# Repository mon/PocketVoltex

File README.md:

# Pocket Voltex

A tiny controller for K-Shoot MANIA/Sound Voltex or other similar games

## Project status
There is a major revision coming sometime 2021 but I estimate requires 50+ hours
to complete design. It will significantly improve manufacturing efficiency and hopefully
allow me to sell controllers while working full-time.

Please don't hold your breath on a timely release, but I have not forgotten this
project.

## Documentation
[DIY Kit assembly](Docs/Assembly.md)  
[(Old version)DIY Kit assembly](Docs/Assembly_old.md)

[Controller configuration](Docs/Configuration.md)

## Features
* Gateron mechanical switches
* Rock solid Bourns encoders with hardware smoothing
* 8 RGB LEDs
* Beautiful laser cut acrylic case
* Custom aluminium knobs by DJ Dao
* Acts as a gamepad or keyboard/mouse (KSM)
* HID Lighting support
* Configurable card/pin macro key
* Chrome configurator
* No drivers required!

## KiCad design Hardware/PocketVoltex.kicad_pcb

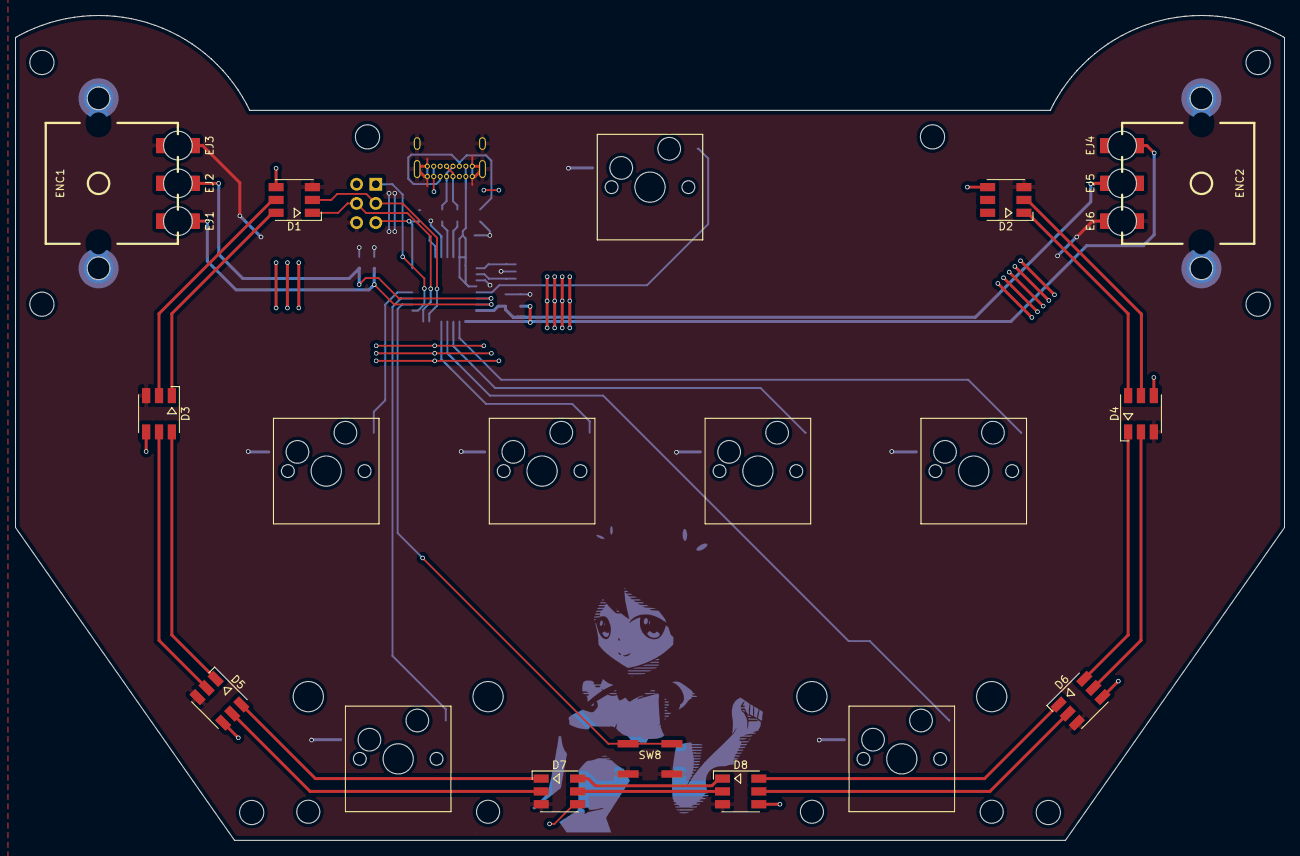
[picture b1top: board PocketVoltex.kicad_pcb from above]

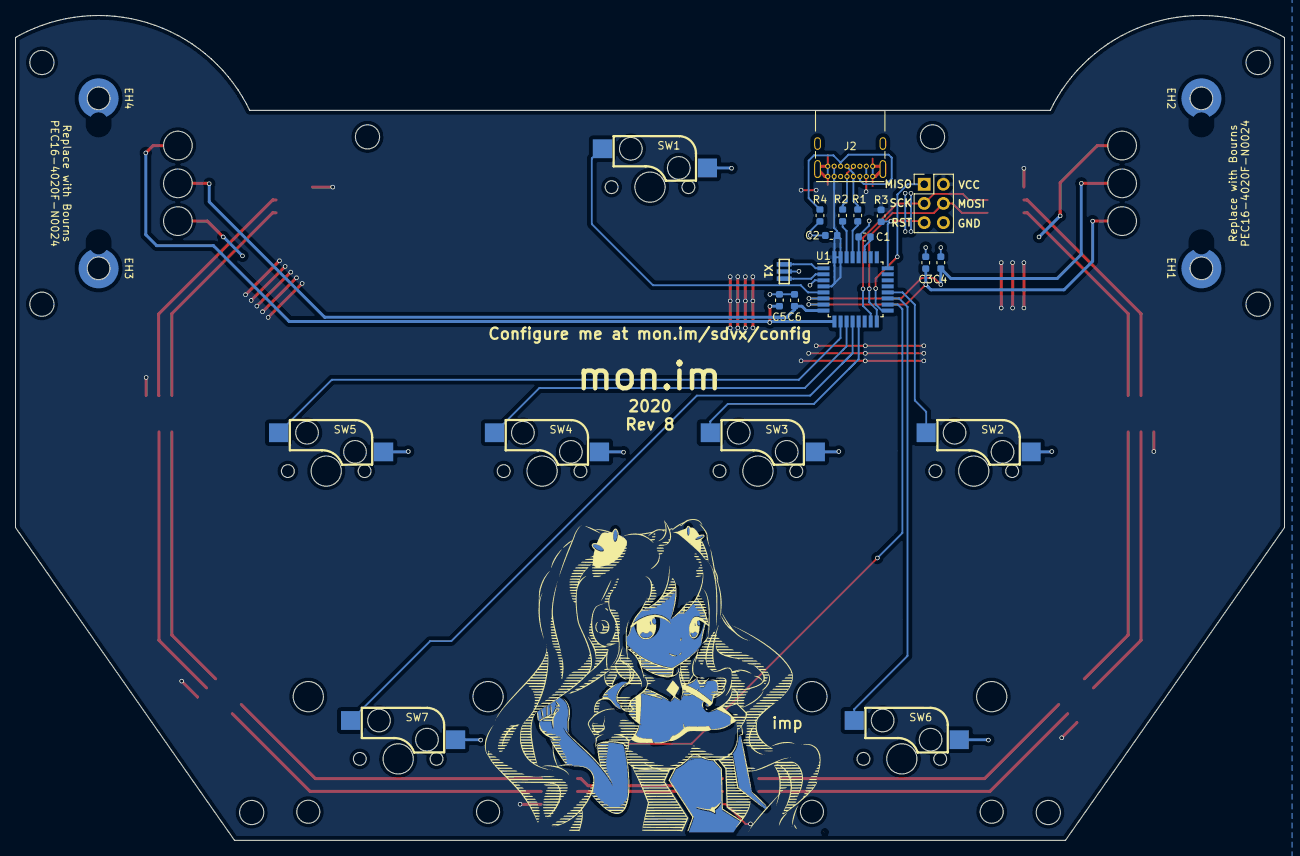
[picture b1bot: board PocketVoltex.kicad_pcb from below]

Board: 2 copper layers, 168.0 x 109.2 mm, 51 parts (19 on the bottom side), 40 nets.

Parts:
C1: 1uF; C_0603_1608Metric
C2: 10uF; C_0603_1608Metric
C3, C4, C5, C6: 10nF; C_0603_1608Metric
D1, D2, D3, D4, D5, D6, D7, D8: SK9822; LED_SK9822
EH1, EH2, EH3, EH4: Encoder nut; SMD_Standoff_M2_Wurth
EJ1, EJ2, EJ3, EJ4, EJ5, EJ6: Hotswap; Harwin-SMD-Socket-S9091-46R
ENC1: VOL_L; Encoder_Bourns_PEC16_hotswap
ENC2: VOL_R; Encoder_Bourns_PEC16_hotswap
H1, H2, H3, H4, H5, H6, H7, H8: MountingHole; MountingHole_3.2mm_M3
J1: Programming header; PinHeader_2x03_P2.54mm_Vertical
J2: USB_C_Receptacle; USB_C_Receptacle_GCT_USB4085
LOGO1: Rasis
R1, R2: 22R; R_0603_1608Metric
R3: 10k; R_0603_1608Metric
R4: 5.1k; R_0603_1608Metric
SW1: MX socket; SW_Cherry_MX1A_1.00u_PCB_Socket
SW2, SW3, SW4, SW5: MX socket; SW_Cherry_MX1A_1.25u_PCB_Socket
SW6, SW7: MX socket; SW_Cherry_MX1A_2.25u_PCB_Socket
SW8: SW_Push; SW_SPST_KSC-J
U1: ATmega32U2-AU; TQFP-32_7x7mm_P0.8mm
X1: 16MHz; murata-resonator_SMD_CSTCE16M0V53-R0

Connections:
/D+: J2.A6, J2.B6, R1.1
/D-: J2.A7, J2.B7, R2.2
/ENC1A: C3.1, EJ1.1, ENC1.A, U1.7
/ENC1B: C4.2, EJ2.1, ENC1.B, U1.6
/ENC2A: C5.1, EJ4.1, ENC2.A, U1.9
/ENC2B: C6.2, EJ5.1, ENC2.B, U1.8
/MISO: J1.1, U1.17
/MOSI: D1.1, J1.4, U1.16
/RESET: J1.5, R3.2, U1.24
/SCLK: D1.2, J1.3, U1.15
/SW_A: SW2.1, U1.20
/SW_B: SW3.1, U1.13
/SW_C: SW4.1, U1.11
/SW_D: SW5.1, U1.10
/SW_FXL: SW6.1, U1.19
/SW_FXR: SW7.1, U1.12
/SW_MACRO: SW8.1, U1.18
/SW_START: SW1.1, U1.5
GND: C1.1, C2.2, C3.2, C4.1, C5.2, C6.1, D1.3, D2.3, D3.3, D4.3, D5.3, D6.3, D7.3, D8.3, EJ3.1, EJ6.1, ENC1.C, ENC2.C, J1.6, J2.A1, J2.A12, J2.B1, J2.B12, J2.S1, R4.1, SW1.2, SW2.2, SW3.2, SW4.2, SW5.2, SW6.2, SW7.2, SW8.2, U1.3, U1.28, X1.2
unnamed: C1.2, U1.27
unnamed: D1.5, D3.2
unnamed: D1.6, D3.1
unnamed: D2.1, D4.6
unnamed: D2.2, D4.5
unnamed: D3.5, D5.2
unnamed: D3.6, D5.1
unnamed: D4.1, D6.6
unnamed: D4.2, D6.5
unnamed: D5.5, D7.2
unnamed: D5.6, D7.1
unnamed: D6.1, D8.6
unnamed: D6.2, D8.5
unnamed: D7.5, D8.2
unnamed: D7.6, D8.1
unnamed: J2.A5, J2.B5, R4.2
unnamed: R1.2, U1.29
unnamed: R2.1, U1.30
unnamed: U1.1, X1.1
unnamed: U1.2, X1.3
VCC: C2.1, D1.4, D2.4, D3.4, D4.4, D5.4, D6.4, D7.4, D8.4, J1.2, J2.A4, J2.A9, J2.B4, J2.B9, R3.1, U1.4, U1.31, U1.32

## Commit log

2016-09-19 Nuke switch LEDs, widen board. WIP
2016-10-25 Wide board complete
2016-10-26 V2 stuff done, initial LED support
2016-10-26 LEDs code now 300% faster
2016-10-28 broke LED descriptor
2016-10-29 Working LEDs
2016-11-11 Case and new encoders
2016-11-22 16MHz, better holes, bigger board, proper microswitch
2016-11-23 Gerber v3
2016-11-23 And the actual zip
2016-12-11 LED patterns, minor improvements
2016-12-16 New board
2016-12-16 Cleanups and memory improvements
2017-01-08 Add macro key on reset switch
2017-01-08 Minor cleanups
2017-01-08 Case improvements
2017-01-08 Rev4 PCB - no LED holes, fixed tenting, slightly bigger encoder holes
2017-01-08 Better encoders (again), better PCB art
2017-01-08 Stronger case
2017-01-08 Better case, nicer art
2017-01-08 gitignore, clean some junk, tabs to whitespace
2017-01-08 Initial WebUSB support
2017-01-08 More knob stability, better lineweights, better switch pos, switch label, smarter hole placement
2017-01-08 Rename firmware folder
2017-01-08 Commit artwork
2017-01-08 Minor cleanup
2017-01-09 Move L1, L2, new resonator, new LED resistors
2017-01-09 Remove Config report in prep for Control based config
2017-01-09 Production commit :)
2017-01-18 Update art and case art to fit within 1mm boundary case to be pretty
2017-01-23 Need that interface after all since top level can't be WinUSB - make it BULK instead of HID since WebUSB
2017-01-23 HID Light setting automation
2017-02-01 Fix libusb connectivity and add more config stuff
2017-02-01 Forgot HandleConfig
2017-02-09 Fix config comunication 🙏
    Turns out using 6 endpoints when you only support 5 is a recipe for disaster
2017-02-09 Slight RAM saving in LED patterns by using a union
2017-02-09 LEDs now high resolution internally and RGB for user, and knobs are stuck on the sides
2017-02-09 Much improved LEDs and persistant knob LEDs
2017-02-10 Knob lights are now gorgeous
2017-02-13 General cleanups, nicer knob code
2017-02-15 Add joystick interface, fix STALL bugs maybe
2017-02-15 Add keylights always, respect config
2017-02-16 1 STALL fixed, 1 to go
2017-02-16 Actually, properly fix stalls
2017-02-16 Fix inline ASM for GCC 4.9
2017-02-17 Breathe mode, LED cleanup and brightness levels increase
2017-02-26 Commit bootloader since we'll modify
2017-03-04 Almost working bootloader
2017-03-04 Bootloader working
2017-03-04 Case adjustments
2017-03-04 Add forgotten bootloader files
2017-03-04 Webconfig commit
2017-03-15 Bootloader, other minor stuff
2017-03-15 Much more case material, may revert if it doesn't fix clack
2017-05-01 Config saving/loading, commit far more of the configurator
2017-05-04 Remove deprecated WebUSB Allowed Origins header
2017-05-20 Better LED patterns
2017-05-21 Better macros, better config, initial updater
2017-05-21 Fix eeprom freeze, LED flash, Macro in config
2017-05-22 Bootloader version that's actually real
2017-05-22 update makefile
2017-05-22 Change config magic to format version
2017-05-26 Config working, add docs
2017-05-26 Add compiled hid lights macro, readme
2017-05-26 Update Hid exe url
2017-05-26 Fix README links
2017-05-26 Add LICENSE
2017-05-26 Consistency
2017-05-30 Nicer key config and logging
2017-06-14 LED soldering clarification
2017-06-16 Add Zadig information
2017-06-16 eAmuse Cloud support
2017-06-27 Add ksm notes
2017-07-21 Prototype for rev5
2017-08-30 Prototype for rev 6
2017-10-06 Much improvement case build process
2017-10-06 Firmware support for rev5 LEDs
2017-10-06 Fix webconfig race condition
2017-10-06 Forgot to add new LED driver files
2017-10-06 Rev6 case updates
2017-10-06 Forgot to init wrapper
2017-12-05 rev6 code fixes
2017-12-09 README update
2018-01-25 DIY docs rev6, firmware tweaks, software tweaks
2018-01-25 Correct links
2018-05-13 Dimensions cleanup in prep
2018-07-07 Fix LED strings
2018-10-29 rev7 - Kicad!
2018-10-29 Add firmware defaults reset, start button LEDs, overall brightness (rev6+)
2018-11-01 Forgot to increment firmware version
2018-11-12 Fix firmware upgrade EEPROM
2018-11-12 Actually update config version, use -Werror
2019-07-07 Kicad 5.1, USB 2.0 C receptacle, CC pulldown
2019-07-07 Change rev to 8
2020-10-28 Commit all the in-progress stuff for a clean slate
2020-10-28 Update (rev7) product shot
2020-10-28 Add info about project status
2021-07-25 Remove obsolete libinput reference
